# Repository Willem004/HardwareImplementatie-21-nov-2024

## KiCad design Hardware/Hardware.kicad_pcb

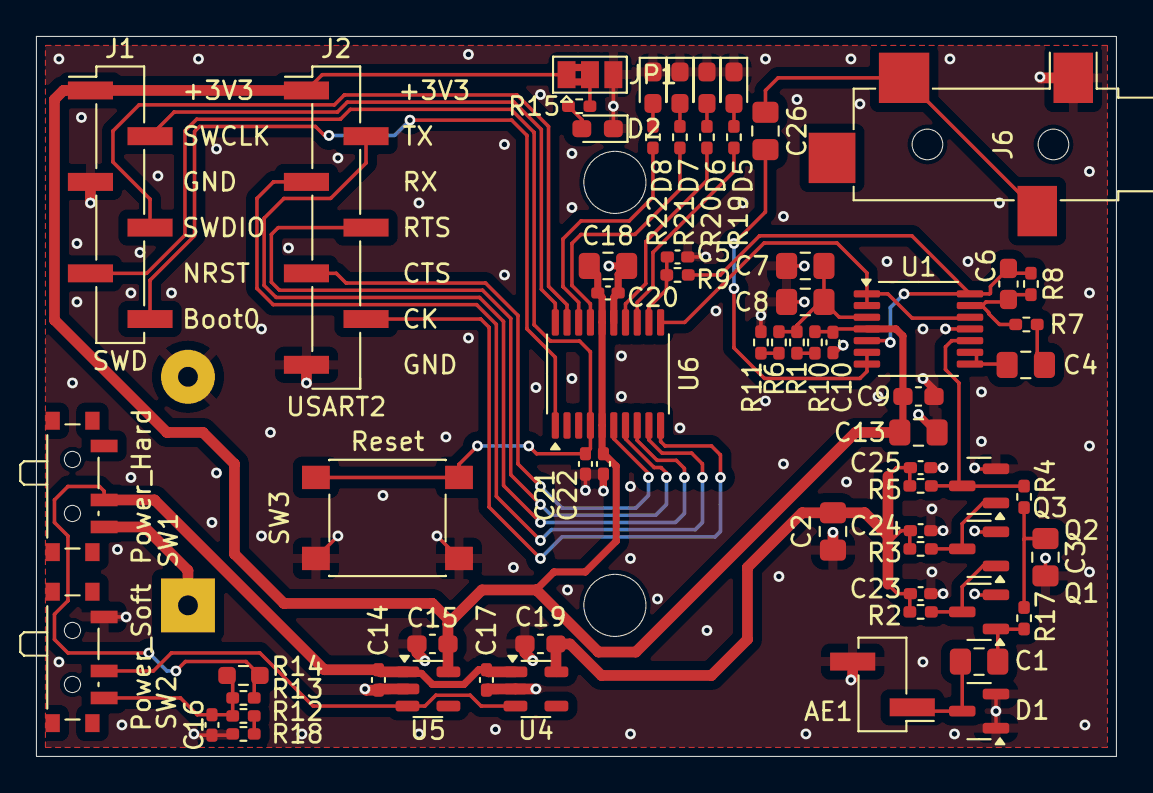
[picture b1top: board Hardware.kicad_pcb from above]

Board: 2 copper layers, 60.0 x 40.0 mm, 67 parts (1 on the bottom side), 44 nets.

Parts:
AE1: Antenna_Shield; PinHeader_1x02_P2.54mm_Vertical_SMD_Pin1Left
BT1: Battery; BatteryHolder_Keystone_2479_3xAAA
C1: 10n; C_0805_2012Metric_Pad1.18x1.45mm_HandSolder
C2, C3: C_Polarized 10µF 16V; C_0805_2012Metric_Pad1.18x1.45mm_HandSolder
C4, C7, C8: 1uF; C_0805_2012Metric_Pad1.18x1.45mm_HandSolder
C5: 150nF; C_0402_1005Metric_Pad0.74x0.62mm_HandSolder
C6: 68pF; C_0603_1608Metric_Pad1.08x0.95mm_HandSolder
C9, C15, C19: 1uF; C_0603_1608Metric_Pad1.08x0.95mm_HandSolder
C10, C14, C16, C17, C20, C21, C22, C23, C24, C25: 100nF; C_0402_1005Metric_Pad0.74x0.62mm_HandSolder
C13, C18, C26: 10uF; C_0805_2012Metric_Pad1.18x1.45mm_HandSolder
D1: BAT54S; SOT-23
D2: LED BLUE, IF≈1mA@2.6V, APT1608LVBx; LED_0603_1608Metric_Pad1.05x0.95mm_HandSolder
D5: LED RED, APT1608LSECK/J3-PRV; LED_0603_1608Metric_Pad1.05x0.95mm_HandSolder
D6: LED ORANGE, APT1608LSECK/J4-PRV; LED_0603_1608Metric_Pad1.05x0.95mm_HandSolder
D7: LED YELLOW, APT1608LSYCK/J3-PRV; LED_0603_1608Metric_Pad1.05x0.95mm_HandSolder
D8: LED GREEN, APT1608LZGCK; LED_0603_1608Metric_Pad1.05x0.95mm_HandSolder
J1: SWD; PinHeader_1x06_P2.54mm_Vertical_SMD_Pin1Left
J2: USART2; PinHeader_1x07_P2.54mm_Vertical_SMD_Pin1Left
J6: AudioJack3_SwitchT; Jack_3.5mm_CUI_SJ-3524-SMT_Horizontal
JP1: Jumper_3_Bridged12; SolderJumper-3_P1.3mm_Bridged2Bar12_Pad1.0x1.5mm
Q1: Q_NPN_BEC BSR17A; SOT-23
Q2, Q3: BC547; SOT-23
R1, R6, R7, R10, R11: 8.2kΩ; R_0402_1005Metric_Pad0.72x0.64mm_HandSolder
R2, R3: 10k; R_0402_1005Metric_Pad0.72x0.64mm_HandSolder
R4, R17: 100k; R_0402_1005Metric_Pad0.72x0.64mm_HandSolder
R5: 1k; R_0402_1005Metric_Pad0.72x0.64mm_HandSolder
R8: 470kΩ; R_0402_1005Metric_Pad0.72x0.64mm_HandSolder
R9: 220Ω; R_0402_1005Metric_Pad0.72x0.64mm_HandSolder
R12, R18: 2MΩ; R_0402_1005Metric_Pad0.72x0.64mm_HandSolder
R13: 39MΩ; R_0402_1005Metric_Pad0.72x0.64mm_HandSolder
R14: 330MΩ preferably 390MΩ; R_0603_1608Metric_Pad0.98x0.95mm_HandSolder
R15: 680Ω; R_0402_1005Metric_Pad0.72x0.64mm_HandSolder
R19, R20, R21: 820Ω; R_0402_1005Metric_Pad0.72x0.64mm_HandSolder
R22: 330Ω; R_0402_1005Metric_Pad0.72x0.64mm_HandSolder
SW1: Power_Hard; SW_SPDT_PCM12
SW2: Power_Soft; SW_SPDT_PCM12
SW3: Reset; SW_Push_1P1T_NO_6x6mm_H9.5mm
U1: Opamp_Quad; TSSOP-14_4.4x5mm_P0.65mm
U4: TLV74115_SOT23-5; SOT-23-5
U5: TLV74133_SOT23-5; SOT-23-5
U6: STM32L010F4Px; TSSOP-20_4.4x6.5mm_P0.65mm

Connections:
+1V5: C2.1, C19.1, C23.1, C24.1, C25.1, R2.1, R3.1, R5.1, U4.5 (OUT)
+3V3: C9.1, C10.1, C13.1, C15.1, C18.1, C20.1, C22.1, J1.1, J2.1, JP1.1 (A), R10.1, U1.4 (V+), U5.5 (OUT), U6.5 (VDDA), U6.16 (VDD)
/MCU/NRST: C21.1, J1.5, SW3.2, U6.4 (NRST)
/MCU/PA0 A0: J2.5, U6.6 (PA0)
/MCU/PA1 A1: J2.4, U6.7 (PA1)
/MCU/PA2 A2: J2.2, U6.8 (PA2)
/MCU/PA3 A3: J2.3, U6.9 (PA3)
/MCU/PA4 A4: J2.6, U6.10 (PA4)
/MCU/PA5 A5: U1.1, U1.2 (-), U1.12 (+), U6.11 (PA5)
/MCU/PA6 A6: C5.1, R9.2, U6.12 (PA6)
/MCU/PA7 A7: R19.2, U6.13 (PA7)
/MCU/PA9: R21.2, U6.17 (PA9)
/MCU/PA10: R22.2, U6.18 (PA10)
/MCU/PA13 SWDIO: J1.4, U6.19 (PA13)
/MCU/PA14 SWCLK: J1.2, U6.20 (PA14)
/MCU/PB1 A9 VREF_OUT: R20.2, U6.14 (PB1)
/MCU/PB9 Boot0: J1.6, U6.1 (PB9)
/Original Smog Detector/Output DC-Coupled: Q3.3 (C), R4.2, R5.2, U1.10 (+)
/PSU/+BATT: BT1.1 (+), SW1.3 (C)
/PSU/+BATT_SWITCH: C14.1, C17.1, R13.2, R14.2, SW1.2 (B), U4.1 (IN), U5.1 (IN)
/PSU/EN: SW2.2 (B), U4.3 (EN), U5.3 (EN)
GND: AE1.2 (Shield), BT1.2 (-), C2.2, C3.2, C5.2, C7.2, C8.2, C9.2, C10.2, C13.2, C14.2, C15.2, C16.2, C17.2, C18.2, C19.2, C20.2, C21.2, C22.2, C23.2, C24.2, C25.2, D1.1 (A), D1.2 (K), D2.1 (K), D5.1 (K), D6.1 (K), D7.1 (K), D8.1 (K), J1.3, J2.7, J6.S, JP1.3 (B), Q1.2 (E), Q2.2 (E), Q3.2 (E), R11.2, R18.2, SW2.1 (A), SW3.1, U1.11 (V-), U4.2 (GND), U5.2 (GND), U6.15 (VSS)
unnamed: AE1.1 (A), C1.1, D1.3 (COM)
unnamed: C3.1, R4.1, R17.2
unnamed: C4.2, R7.1
unnamed: C26.2, J6.R, J6.T
unnamed: D2.2 (A), R15.2
unnamed: D5.2 (A), R19.1
unnamed: D6.2 (A), R20.1
unnamed: D7.2 (A), R21.1
unnamed: D8.2 (A), R22.1
unnamed: JP1.2 (C), R15.1
unnamed: C1.2, Q1.1 (B), R17.1
unnamed: Q1.3 (C), Q2.1 (B), R2.2
unnamed: Q2.3 (C), Q3.1 (B), R3.2
unnamed: R1.1, R10.2
unnamed: R6.2, R11.1
unnamed: R12.2, R18.1
unnamed: C16.1, R12.1, R13.1, R14.1, SW2.3 (C)
unnamed: C7.1, C8.1, R1.2, R6.1, U1.3 (+)
unnamed: C6.2, R8.2, R9.1, U1.5 (+), U1.14
unnamed: C26.1, U1.6 (-), U1.7
unnamed: C4.1, U1.8, U1.9 (-)
unnamed: C6.1, R7.2, R8.1, U1.13 (-)

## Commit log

2024-11-21 Started project in KiCad
2024-11-21 added notes folder with Markdown document
2024-11-21 added .lck files to .gitignore
2024-11-25 Made sheet "Original Smog Detector"
    Added a new hierarchical sheet to the root sheet
2024-11-25 Redrew the original circuit without the battery, switch and output jack
2024-12-02 Started MCU sheet, Might be way overkill
2024-12-02 Changed power labels to hierarchical labels and DC coupled the output
2024-12-02 Made sheet Signal Amplification
    will handle
    - AC coupling of input
    - DC biasing to 3V3/2
    - Amplification by approx *-60
    - Lowpass based anti-aliasing
2024-12-02 Drew the analog Signal conditioning
    The analog signal conditioning can be reduced to:
    - a amplification by -60
    - a High-Pass filter with Fc≈20Hz -3dB
    - a Low-Pass filter with Fc≈5kHz -6dB
2024-12-02 split some of the text and grouped the circuits better
2024-12-05 made sheet PSU for power management
2024-12-05 made symbols for TLV741 voltage regulator
2024-12-05 started regulator circuit, EN circuit is not finished yet
2024-12-07 Did to much for one commit BAD
    - calculated values for EN divider in PSU sheet
    - added power flag to switch output in PSU sheet
    - connected the different sheets in the Root page
2024-12-07 added power led to 3V3 and explained why it's not possible for 1V5 with a simple circuit
2024-12-07 made sheet MCU
2025-01-06 changed "Output Bias1V65" to "OUT Signal Bias1V65"
2025-01-06 Linked ampliefier sheet with mcu sheet
2025-01-06 Added cheapest STM32L0 from mouser and mapped USART UART SPI and I2C to headers
2025-01-25 Added reset button to mcu sheet
2025-01-25 changed duplicate resistor reference designator from R2 to R17
2025-01-25 Started linking footprints and work on the pcb layout
2025-01-25 added more footprints and continued on the circuit diagram
    - [ ] add antenna connection
    - [ ] find suitable 390Mohm resistor
    - [ ] add switches, reset and power
2025-01-26 changed must solder bridges to do not populate due to lack of space
    removed from board
    do not populate (dnr)
    exclude from bom
2025-01-26 PCB is done???
2025-01-26 Gestart met verslag
2025-01-29 Verslag, zin opbouw verbeterd
2025-01-29 Added headphone output to schematic
2025-01-29 added headphone jack footprint, SJ-3524-SMT
2025-01-29 PCB layed-out
    - [x] headphone jack
    - [x] UART header
    - [x] Only one power trace with sub optimal return path
2025-01-29 added four leds
2025-01-29 closed KiCad
2025-01-30 The inverting opamp was fixed wrong now it's fixed in the schematic
2025-01-30 Inverting opamp is now also fixed on the PCB
2025-01-30 Changed text to match resistor values for regulator enable divider
2025-01-30 Moved an outline a bit
2025-01-30 Changed text PSU EN switch to match circuit
2025-01-30 Moved some labels in PSU
2025-01-30 Screenshots toegevoegd van het schema
2025-01-30 Added two pictures of the PCB
